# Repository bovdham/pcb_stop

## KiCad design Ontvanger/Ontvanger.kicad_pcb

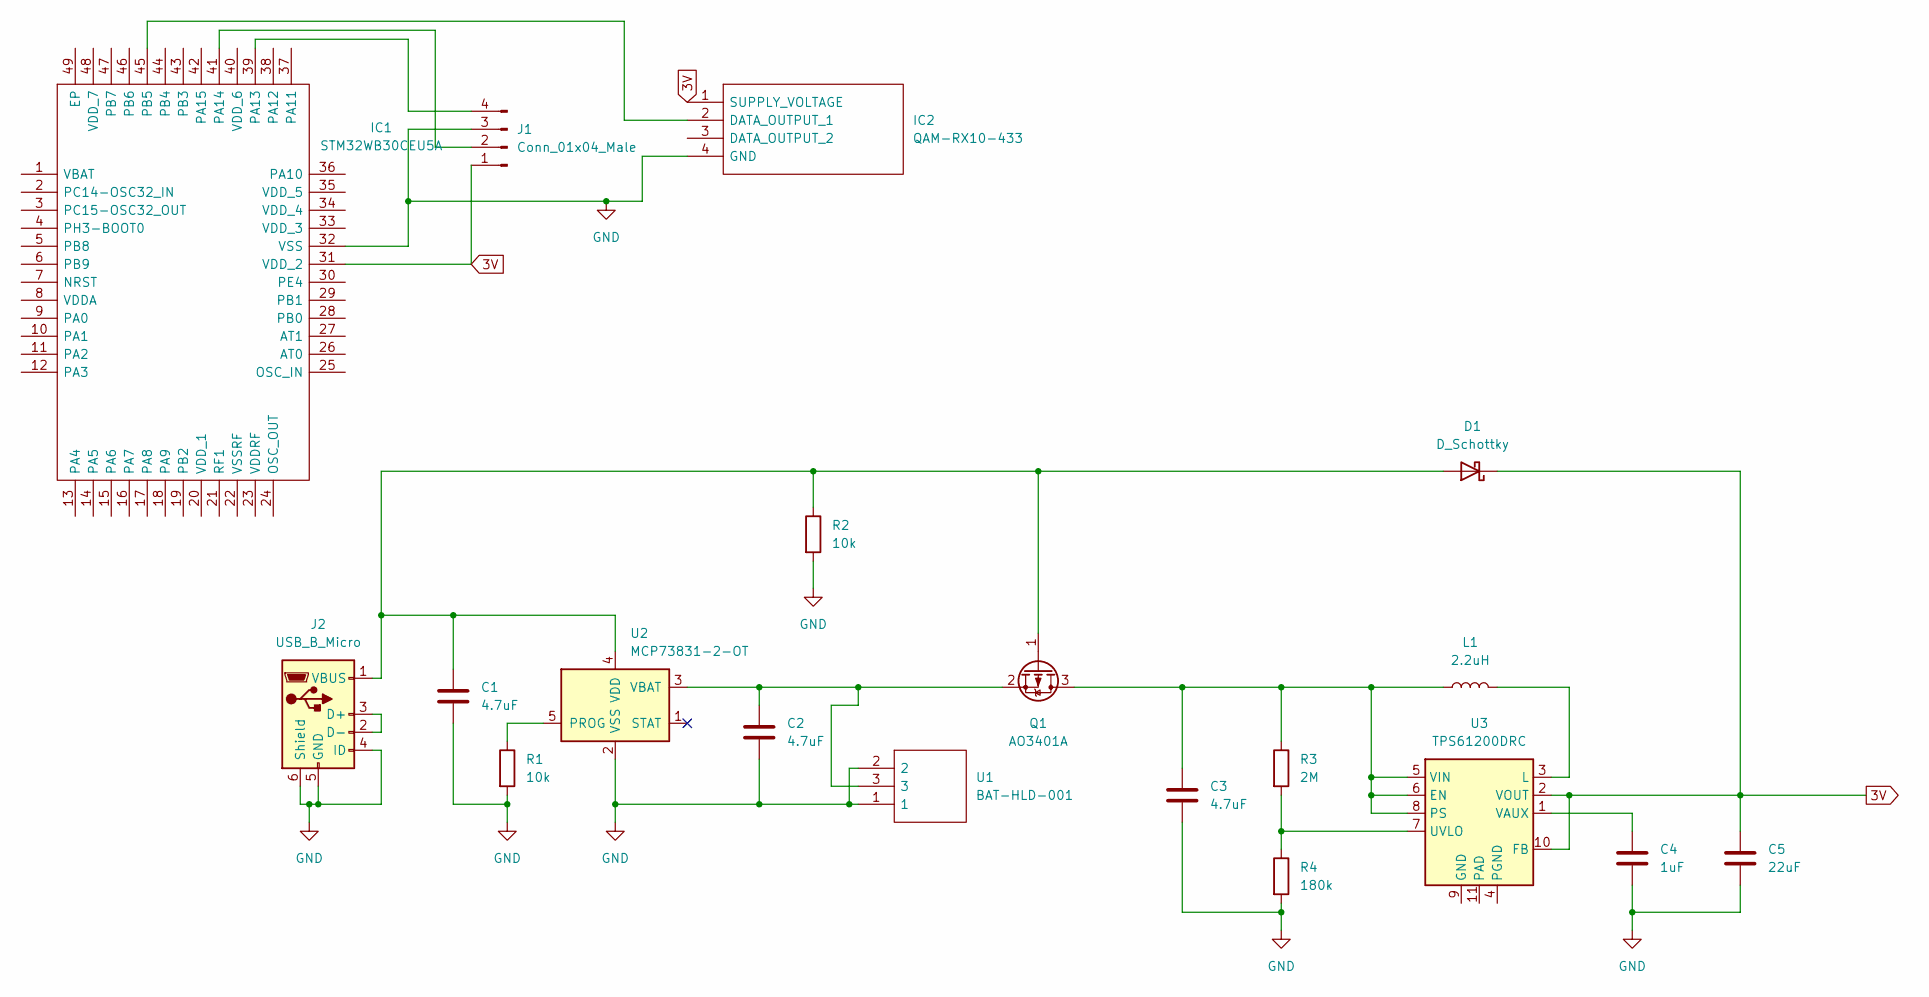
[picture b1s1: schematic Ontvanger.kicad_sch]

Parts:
C1, C2, C3: 4.7uF; C_0402_1005Metric
C4: 1uF; C_0402_1005Metric
C5: 22uF; C_0402_1005Metric
D1: D_Schottky; D_0402_1005Metric
IC1: STM32WB30CEU5A; QFN50P700X700X60-49N-D; Mouser Part Number 511-STM32WB30CEU5A
IC2: QAM-RX10-433; QAMRX10433; Mouser Part Number 223-QAM-RX10-433
J1: Conn_01x04_Male; PinHeader_1x04_P1.00mm_Vertical
J2: USB_B_Micro; USB_Micro-B_Molex-105133-0001
L1: 2.2uH; L_0402_1005Metric
Q1: AO3401A; SOT-23
R1, R2: 10k; R_0201_0603Metric
R3: 2M; R_0201_0603Metric
R4: 180k; R_0201_0603Metric
U1: BAT-HLD-001; BATHLD001; Mouser Part Number 712-BAT-HLD-001
U2: MCP73831-2-OT; SOT-23-5
U3: TPS61200DRC; Texas_S-PVSON-N10_ThermalVias

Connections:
3V: C5.1, D1.1 (K), IC1.31 (VDD_2), IC2.1 (SUPPLY_VOLTAGE), J1.1, U3.2 (VOUT), U3.10 (FB)
GND: C1.2, C2.2, C3.2, C4.2, C5.2, IC1.32 (VSS), IC2.4 (GND), J1.3, J2.4 (ID), J2.5 (GND), J2.6 (Shield), R1.2, R2.2, R4.2, U1.1, U1.2, U2.2 (VSS)
unnamed: C1.1, D1.2 (A), J2.1 (VBUS), Q1.1 (G), R2.1, U2.4 (VDD)
unnamed: C2.1, Q1.2 (S), U1.3, U2.3 (VBAT)
unnamed: C3.1, L1.1, Q1.3 (D), R3.1, U3.5 (VIN), U3.6 (EN), U3.8 (PS)
unnamed: C4.1, U3.1 (VAUX)
unnamed: IC1.39 (PA13), J1.4
unnamed: IC1.41 (PA14), J1.2
unnamed: IC1.45 (PB5), IC2.2 (DATA_OUTPUT_1)
unnamed: J2.2 (D-), J2.3 (D+)
unnamed: L1.2, U3.3 (L)
unnamed: R1.1, U2.5 (PROG)
unnamed: R3.2, R4.1, U3.7 (UVLO)

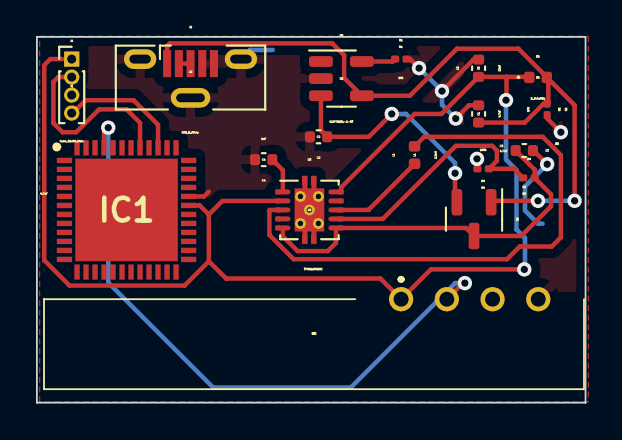
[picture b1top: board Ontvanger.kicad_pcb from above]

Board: 2 copper layers, 30.5 x 20.3 mm, 19 parts (1 on the bottom side), 13 nets.

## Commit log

2022-05-09 added initial files
2022-05-16 filss added
